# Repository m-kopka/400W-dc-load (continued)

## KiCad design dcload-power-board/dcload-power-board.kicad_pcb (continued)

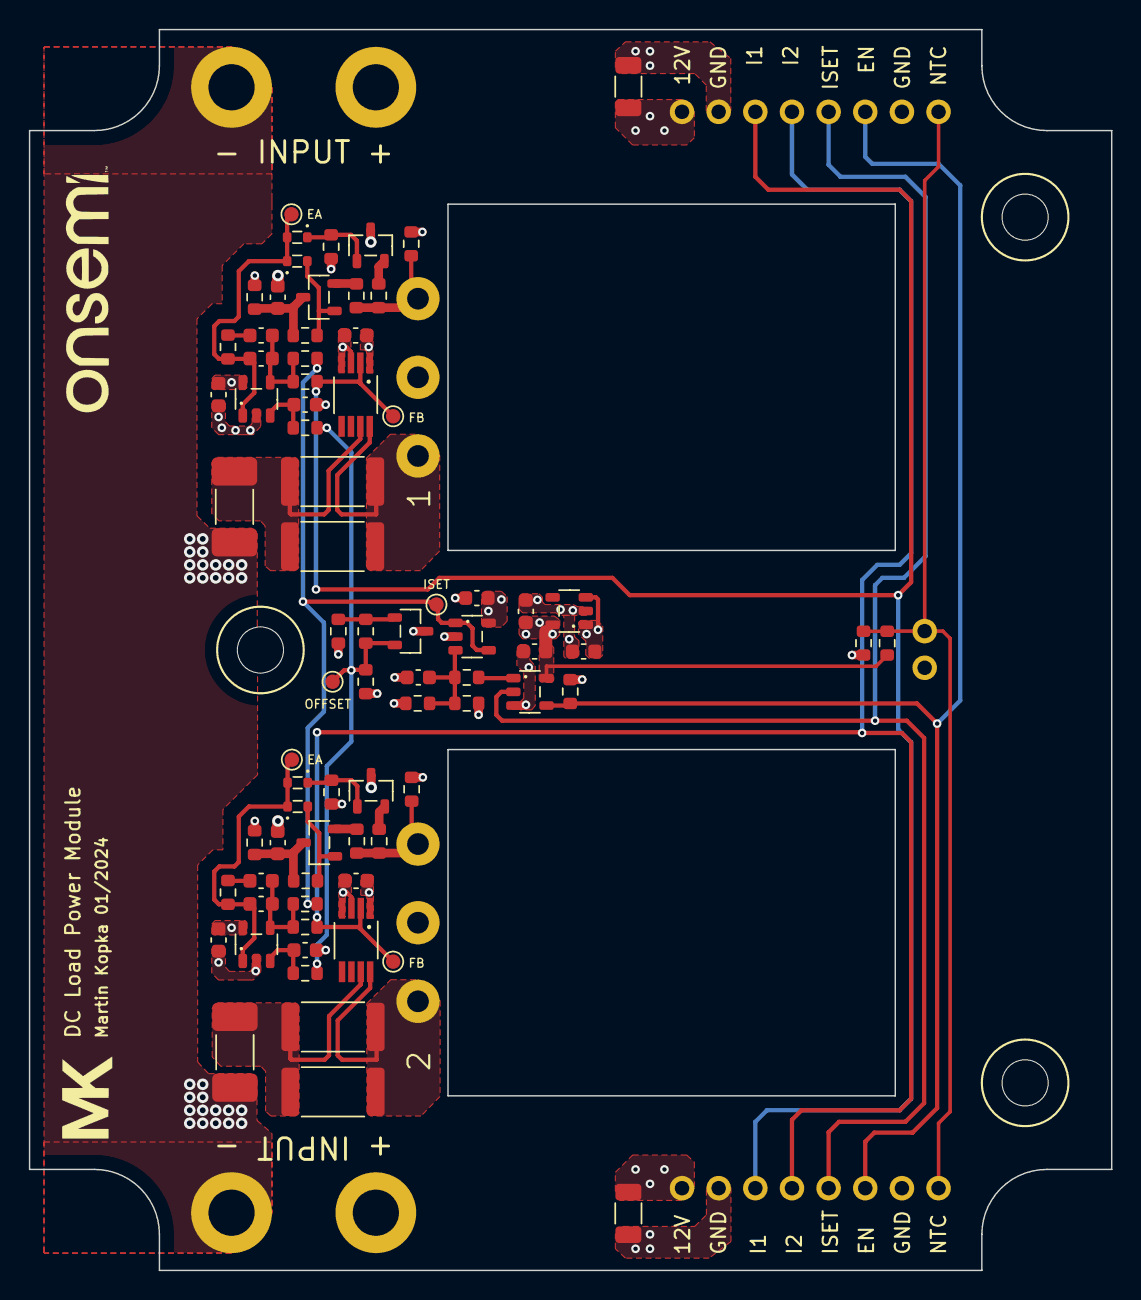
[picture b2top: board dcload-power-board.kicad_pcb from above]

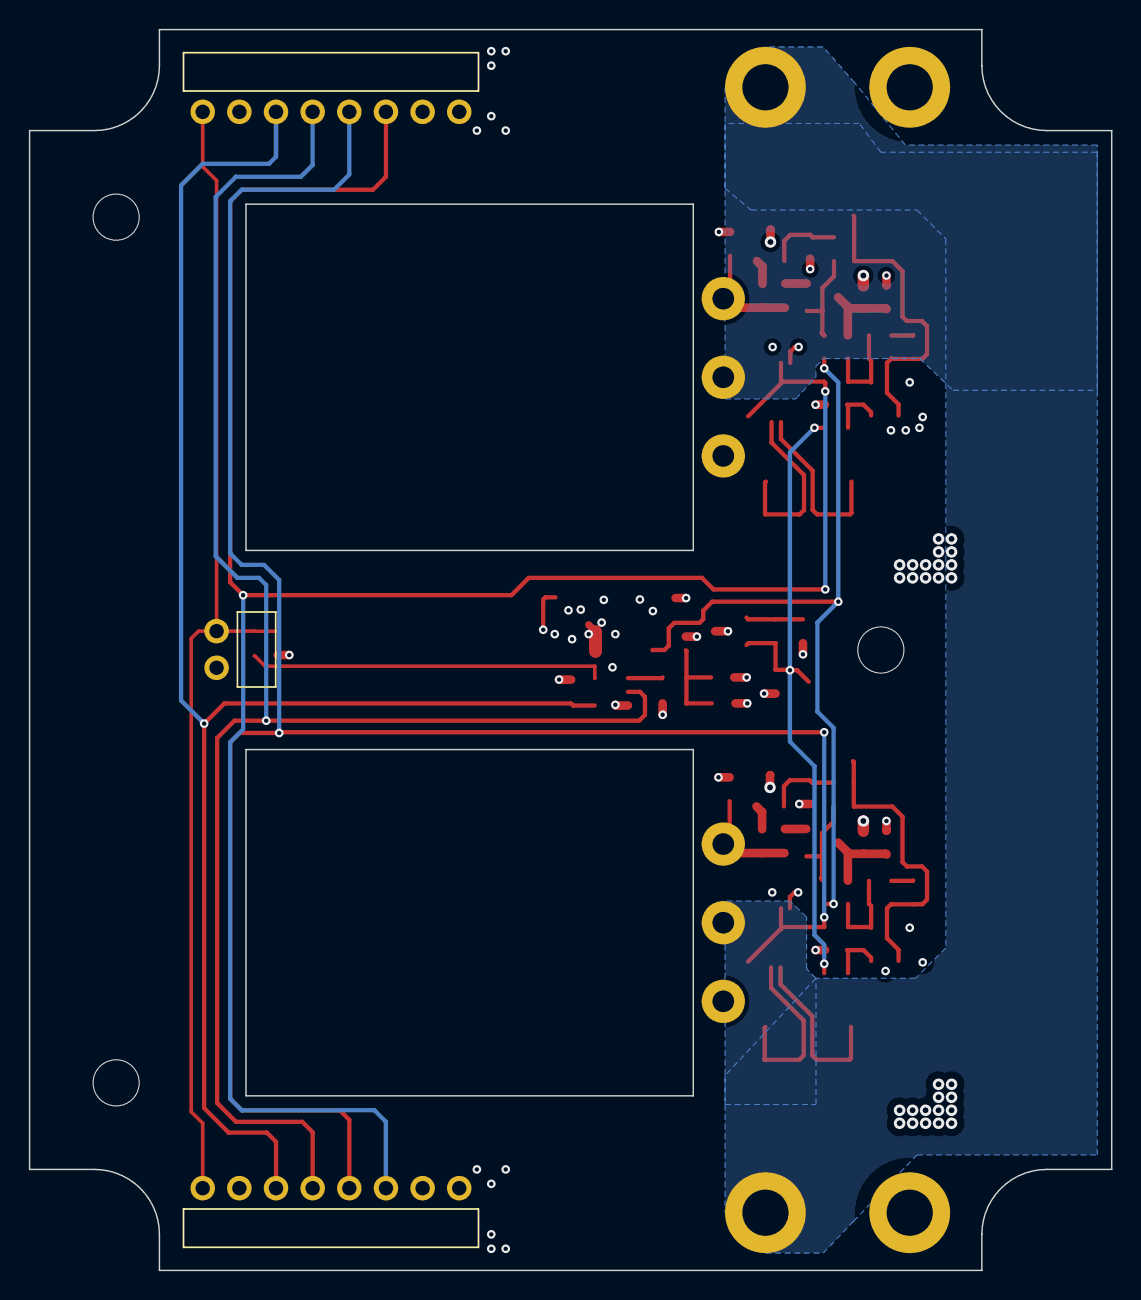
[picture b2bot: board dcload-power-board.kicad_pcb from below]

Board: 4 copper layers, 75.0 x 86.0 mm, 88 parts (3 on the bottom side), 38 nets.

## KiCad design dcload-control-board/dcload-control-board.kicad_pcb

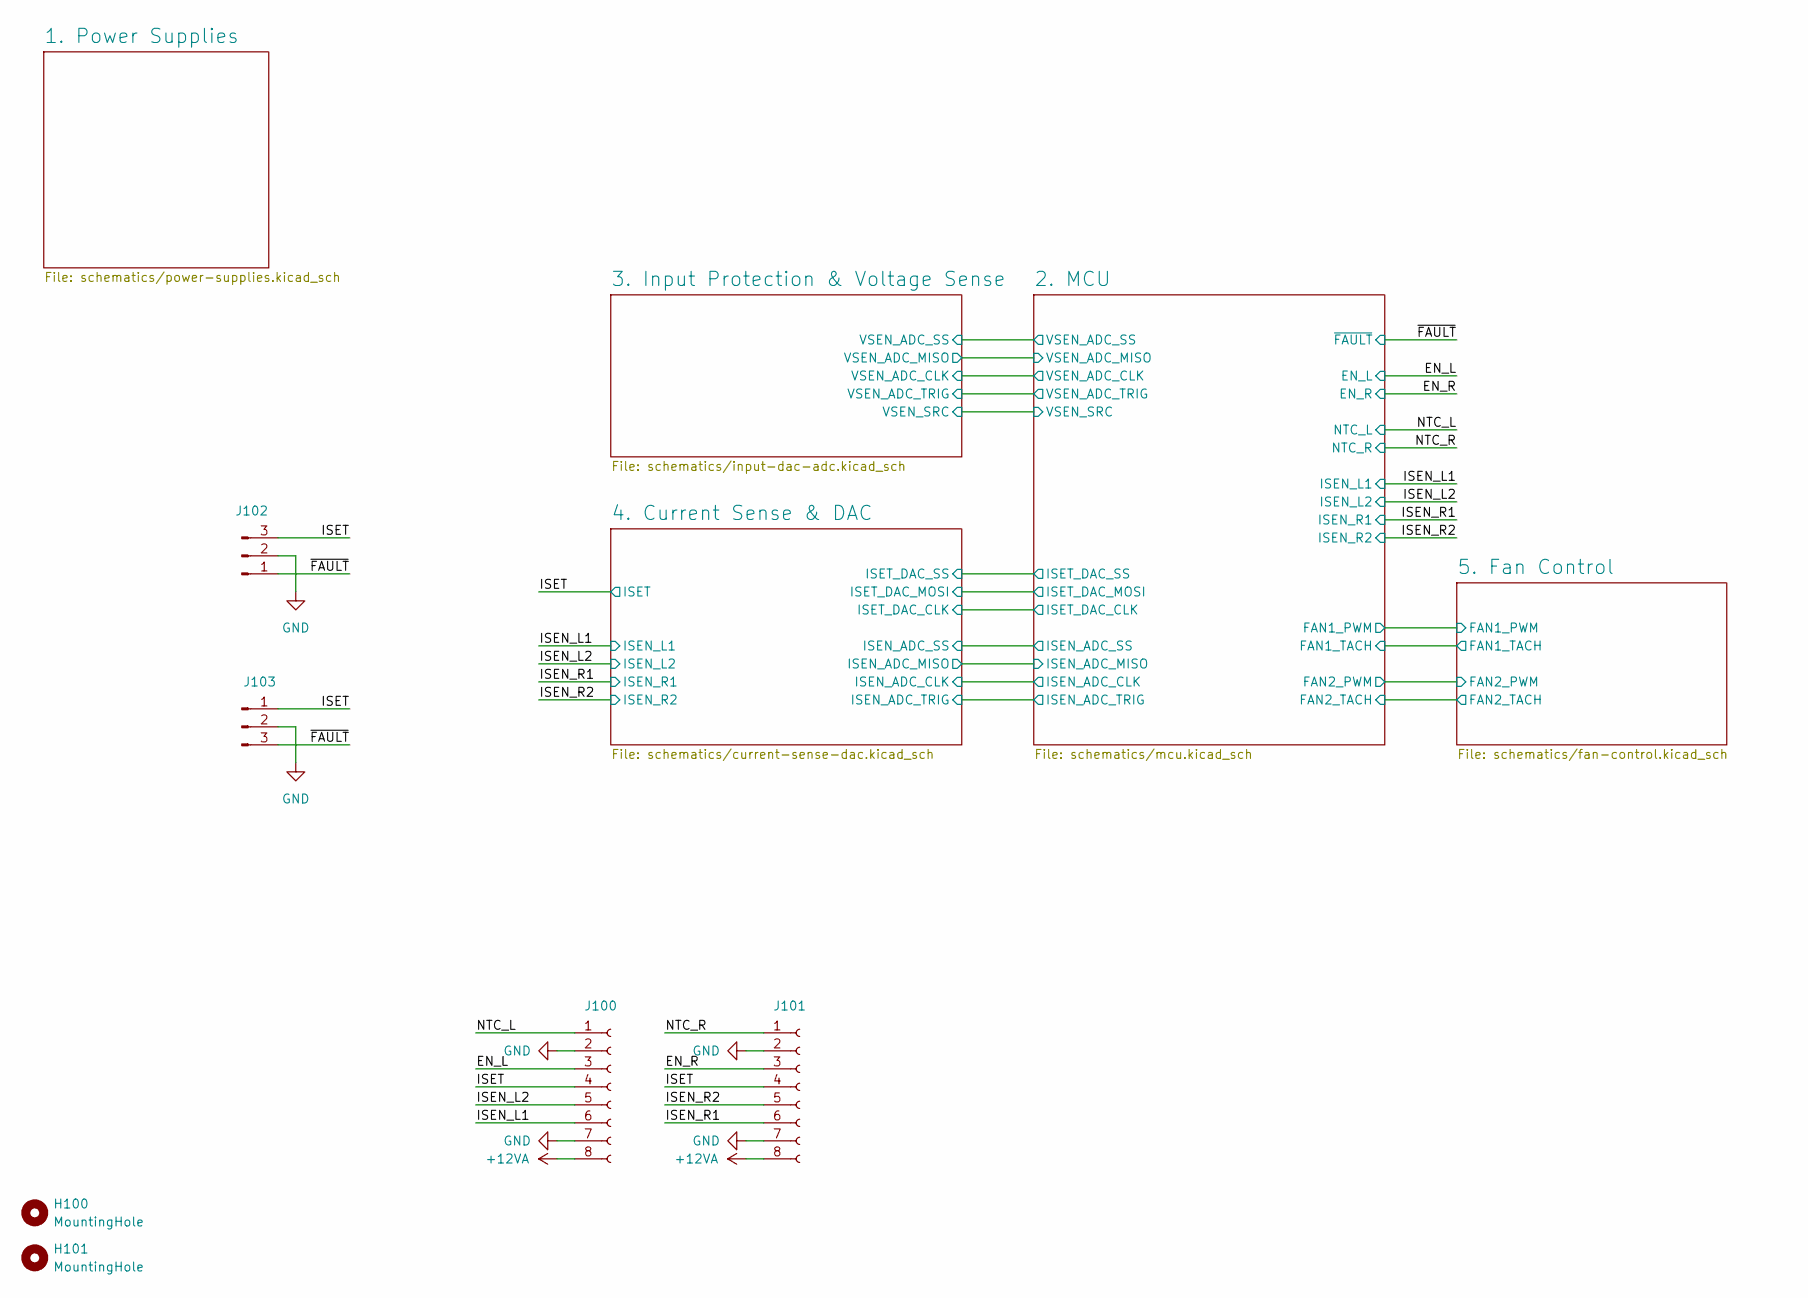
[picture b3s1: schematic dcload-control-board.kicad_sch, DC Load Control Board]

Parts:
H100, H101: MountingHole; MountingHole_3.2mm_M3
J100, J101: Conn_01x08_Female; PinSocket_1x08_P2.54mm_Vertical
J102, J103: Conn_01x03_Male; PinHeader_1x03_P2.54mm_Horizontal

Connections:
+12VA: J100.8, J101.8; also elsewhere on the board
/EN_L: J100.3; also elsewhere on the board
/EN_R: J101.3; also elsewhere on the board
/ISEN_L1: J100.6; also elsewhere on the board
/ISEN_L2: J100.5; also elsewhere on the board
/ISEN_R1: J101.6; also elsewhere on the board
/ISEN_R2: J101.5; also elsewhere on the board
/ISET: J100.4, J101.4, J102.3, J103.1; also elsewhere on the board
/NTC_L: J100.1; also elsewhere on the board
/NTC_R: J101.1; also elsewhere on the board
/~FAULT: J102.1, J103.3; also elsewhere on the board
GND: J100.2, J100.7, J101.2, J101.7, J102.2, J103.2; also elsewhere on the board

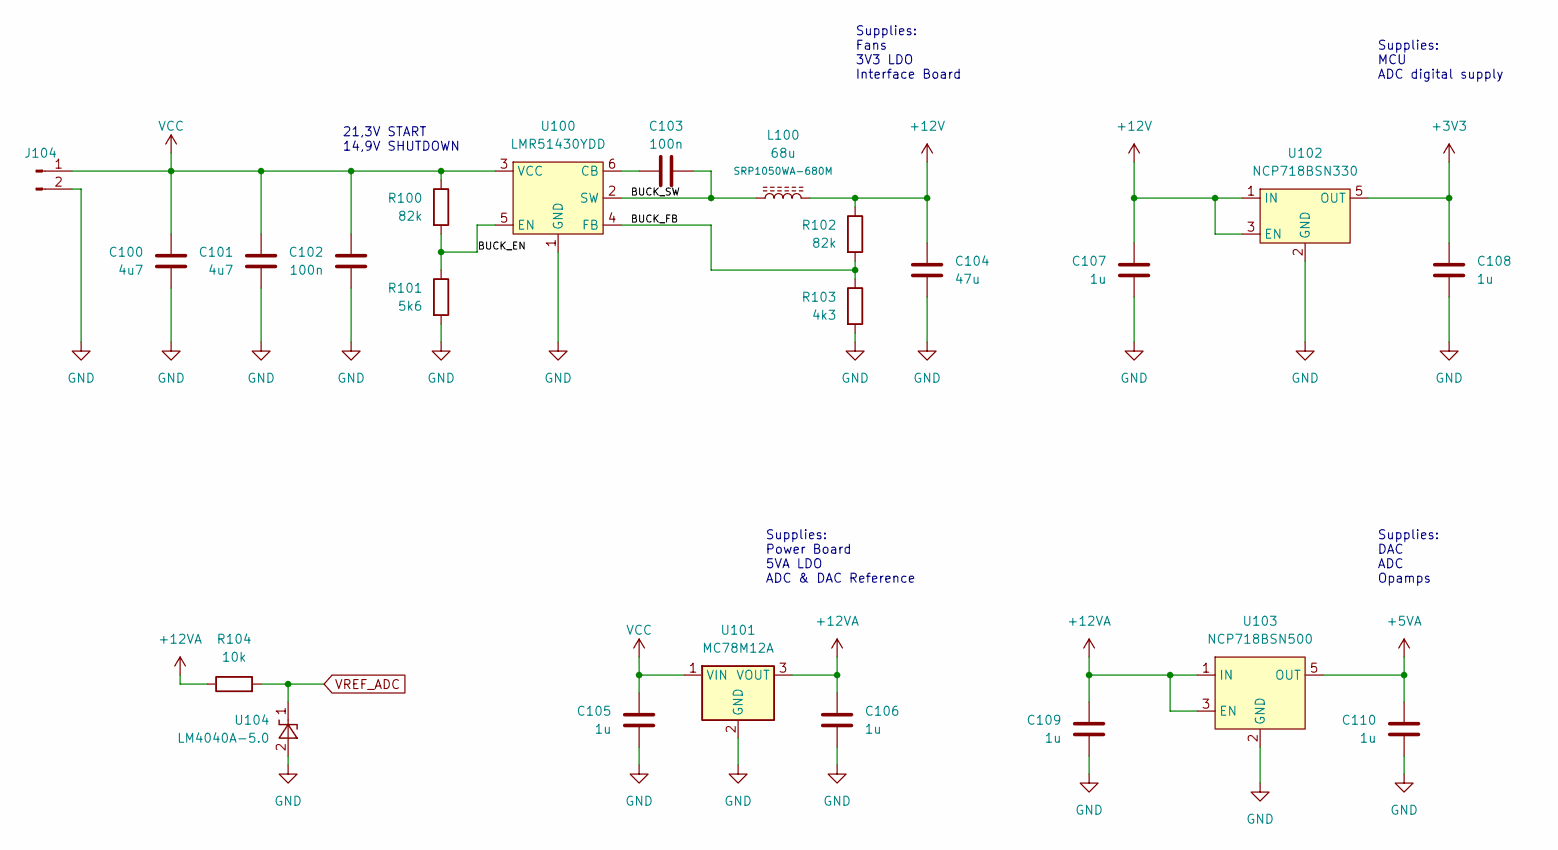
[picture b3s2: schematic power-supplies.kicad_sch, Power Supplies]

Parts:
C100, C101: 4u7; C_1206_3216Metric
C102, C103: 100n; C_0603_1608Metric
C104: 47u; C_1206_3216Metric
C105: 1u; C_1206_3216Metric
C106, C107, C108, C109, C110: 1u; C_0603_1608Metric
J104: Conn_01x02_Male; KLS PSH02-02W
L100: 68u; L_10.4x10.4_H4.8
R100, R102: 82k; R_0603_1608Metric
R101: 5k6; R_0603_1608Metric
R103: 4k3; R_0603_1608Metric
R104: 10k; R_0603_1608Metric
U100: LMR51430YDD; SOP-6
U101: MC78M12A; TO-252-2
U102: NCP718BSN330; SOT-23-5L
U103: NCP718BSN500; SOT-23-5L
U104: LM4040A-5.0; SOT-23

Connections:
+3V3: C108.2, U102.5 (OUT); also elsewhere on the board
+5VA: C110.2, U103.5 (OUT); also elsewhere on the board
+12V: C104.1, C107.2, L100.2, R102.1, U102.1 (IN), U102.3 (EN); also elsewhere on the board
+12VA: C106.2, C109.2, R104.1, U101.3 (VOUT), U103.1 (IN), U103.3 (EN); also elsewhere on the board
/1. Power Supplies/BUCK_EN: R100.2, R101.1, U100.5 (EN)
/1. Power Supplies/BUCK_FB: R102.2, R103.1, U100.4 (FB)
/1. Power Supplies/BUCK_SW: C103.2, L100.1, U100.2 (SW)
GND: C100.2, C101.2, C102.2, C104.2, C105.1, C106.1, C107.1, C108.1, C109.1, C110.1, J104.2, R101.2, R103.2, U100.1 (GND), U101.2 (GND), U102.2 (GND), U103.2 (GND), U104.2 (A); also elsewhere on the board
unnamed: C103.1, U100.6 (CB)
VCC: C100.1, C101.1, C102.1, C105.2, J104.1, R100.1, U100.3 (VCC), U101.1 (VIN)
VREF_ADC: R104.2, U104.1 (K); also elsewhere on the board

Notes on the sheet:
Supplies: Power Board 5VA LDO ADC & DAC Reference
Supplies: DAC ADC Opamps
21,3V START 14,9V SHUTDOWN
Supplies: MCU ADC digital supply
Supplies: Fans 3V3 LDO Interface Board

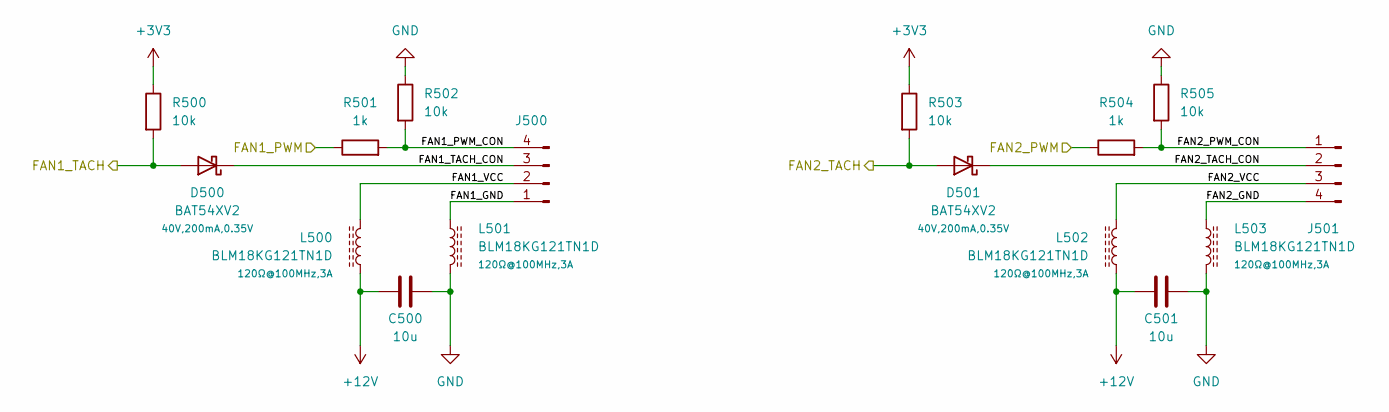
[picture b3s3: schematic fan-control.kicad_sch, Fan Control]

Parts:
C500, C501: 10u; C_1206_3216Metric
D500, D501: BAT54XV2; SOD-523
J500, J501: Conn_01x04_Male; PinHeader_1x04_P2.54mm_Horizontal
L500, L501, L502, L503: BLM18KG121TN1D; R_0603_1608Metric
R500, R502, R503, R505: 10k; R_0603_1608Metric
R501, R504: 1k; R_0603_1608Metric

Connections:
+3V3: R500.1, R503.1; also elsewhere on the board
+12V: C500.1, C501.1, L500.1, L502.1; also elsewhere on the board
/2. MCU/FAN1_PWM: R501.1; also elsewhere on the board
/2. MCU/FAN1_TACH: D500.2 (A), R500.2; also elsewhere on the board
/2. MCU/FAN2_PWM: R504.1; also elsewhere on the board
/2. MCU/FAN2_TACH: D501.2 (A), R503.2; also elsewhere on the board
/5. Fan Control/FAN1_GND: J500.1, L501.1
/5. Fan Control/FAN1_PWM_CON: J500.4, R501.2, R502.2
/5. Fan Control/FAN1_TACH_CON: D500.1 (K), J500.3
/5. Fan Control/FAN1_VCC: J500.2, L500.2
/5. Fan Control/FAN2_GND: J501.4, L503.1
/5. Fan Control/FAN2_PWM_CON: J501.1, R504.2, R505.2
/5. Fan Control/FAN2_TACH_CON: D501.1 (K), J501.2
/5. Fan Control/FAN2_VCC: J501.3, L502.2
GND: C500.2, C501.2, L501.2, L503.2, R502.1, R505.1; also elsewhere on the board

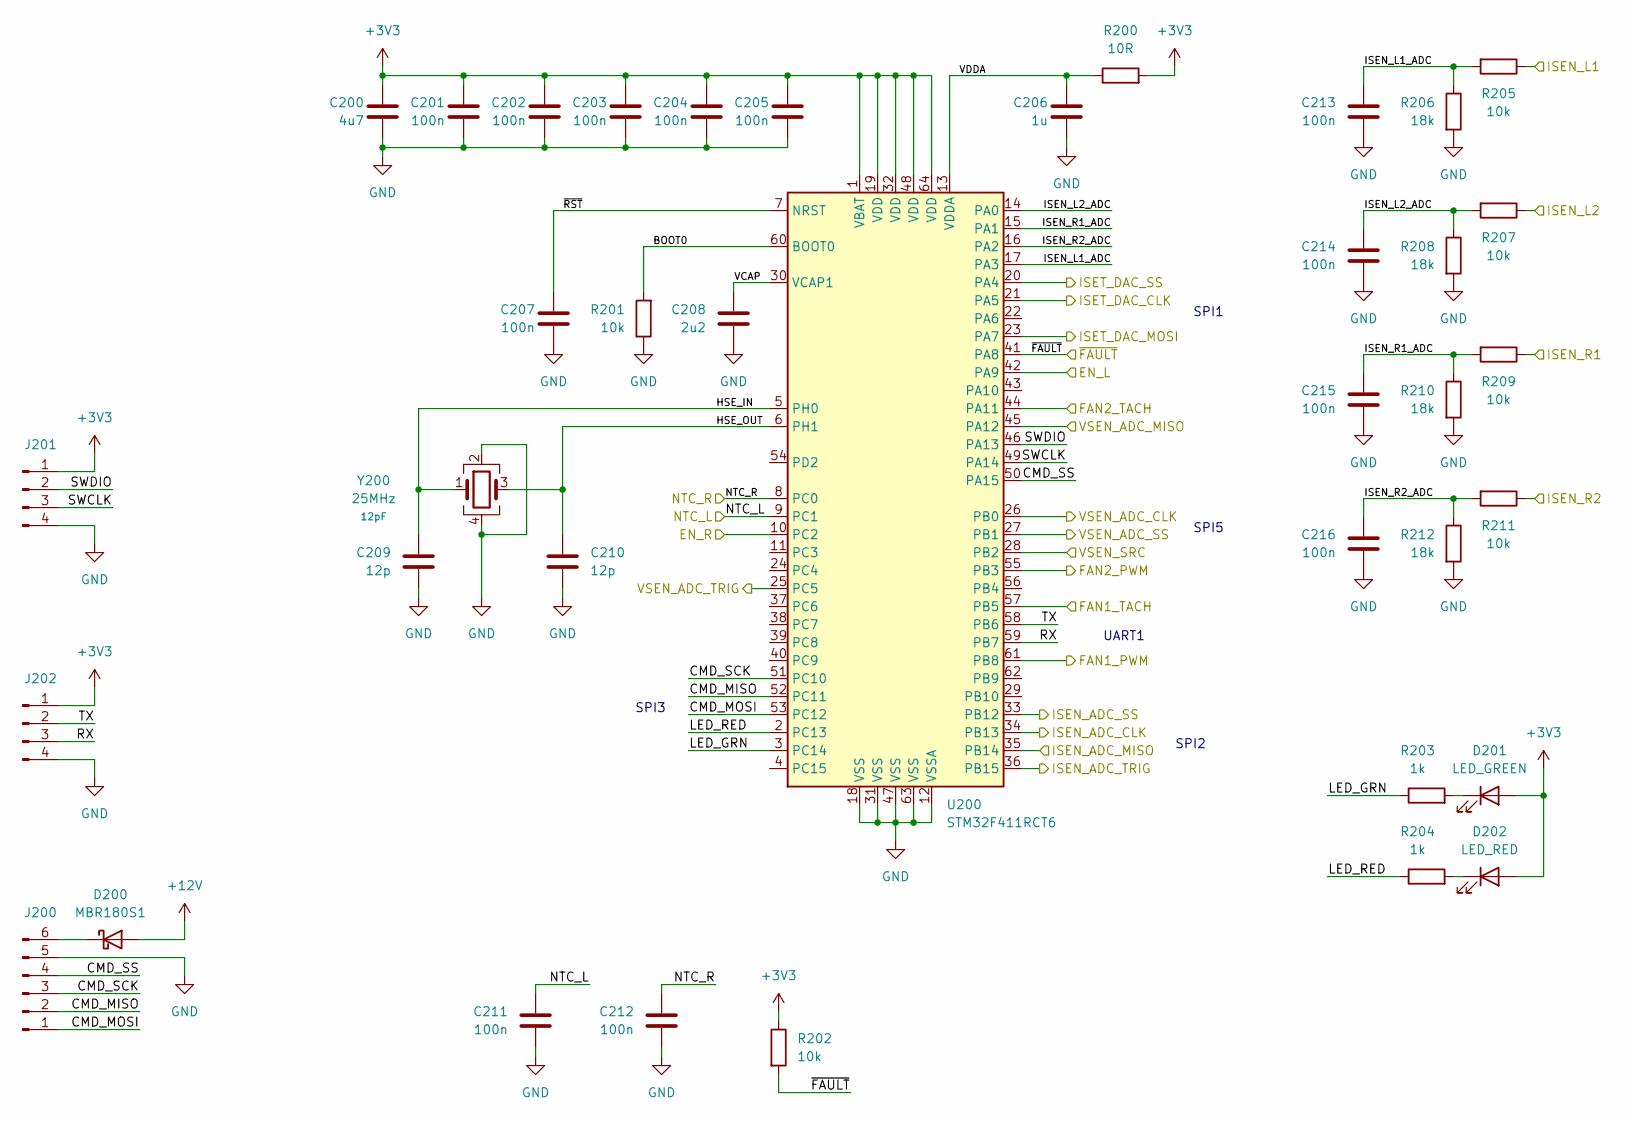
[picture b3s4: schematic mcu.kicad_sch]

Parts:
C200: 4u7; C_0603_1608Metric
C201, C202, C203, C204, C205, C207, C211, C212, C213, C214, C215, C216: 100n; C_0603_1608Metric
C206: 1u; C_0603_1608Metric
C208: 2u2; C_0603_1608Metric
C209, C210: 12p; C_0603_1608Metric
D200: MBR180S1; SOD-123LF
D201: LED_GREEN; LED 0603
D202: LED_RED; LED 0603
J200: Conn_01x06_Male; PinHeader_1x06_P2.54mm_Horizontal
J201, J202: Conn_01x04_Male; PinHeader_1x04_P2.54mm_Vertical
R200: 10R; R_0603_1608Metric
R201, R202, R205, R207, R209, R211: 10k; R_0603_1608Metric
R203, R204: 1k; R_0603_1608Metric
R206, R208, R210, R212: 18k; R_0603_1608Metric
U200: STM32F411RCT6; LQFP-64_10x10mm_P0.5mm
Y200: 25MHz; Crystal 3225 3.2x2.5mm 4pin; Part ECS-250-12-33-AGN-TR3

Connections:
+3V3: C200.1, C201.1, C202.1, C203.1, C204.1, C205.1, D201.2 (A), D202.2 (A), J201.1, J202.1, R200.2, R202.1, U200.1 (VBAT), U200.19 (VDD), U200.32 (VDD), U200.48 (VDD), U200.64 (VDD); also elsewhere on the board
+12V: D200.2 (A); also elsewhere on the board
/2. MCU/BOOT0: R201.2, U200.60 (BOOT0)
/2. MCU/CMD_MISO: J200.2, U200.52 (PC11)
/2. MCU/CMD_MOSI: J200.1, U200.53 (PC12)
/2. MCU/CMD_SCK: J200.3, U200.51 (PC10)
/2. MCU/CMD_SS: J200.4, U200.50 (PA15)
/2. MCU/FAN1_PWM: U200.61 (PB8); also elsewhere on the board
/2. MCU/FAN1_TACH: U200.57 (PB5); also elsewhere on the board
/2. MCU/FAN2_PWM: U200.55 (PB3); also elsewhere on the board
/2. MCU/FAN2_TACH: U200.44 (PA11); also elsewhere on the board
/2. MCU/HSE_IN: C209.1, U200.5 (PH0), Y200.1
/2. MCU/HSE_OUT: C210.1, U200.6 (PH1), Y200.3
/2. MCU/ISEN_ADC_CLK: U200.34 (PB13); also elsewhere on the board
/2. MCU/ISEN_ADC_MISO: U200.35 (PB14); also elsewhere on the board
/2. MCU/ISEN_ADC_SS: U200.33 (PB12); also elsewhere on the board
/2. MCU/ISEN_ADC_TRIG: U200.36 (PB15); also elsewhere on the board
/2. MCU/ISEN_L1_ADC: C213.1, R205.2, R206.1, U200.17 (PA3)
/2. MCU/ISEN_L2_ADC: C214.1, R207.2, R208.1, U200.14 (PA0)
/2. MCU/ISEN_R1_ADC: C215.1, R209.2, R210.1, U200.15 (PA1)
/2. MCU/ISEN_R2_ADC: C216.1, R211.2, R212.1, U200.16 (PA2)
/2. MCU/ISET_DAC_CLK: U200.21 (PA5); also elsewhere on the board
/2. MCU/ISET_DAC_MOSI: U200.23 (PA7); also elsewhere on the board
/2. MCU/ISET_DAC_SS: U200.20 (PA4); also elsewhere on the board
/2. MCU/LED_GRN: R203.1, U200.3 (PC14)
/2. MCU/LED_RED: R204.1, U200.2 (PC13)
/2. MCU/RX: J202.3, U200.59 (PB7)
/2. MCU/SWCLK: J201.3, U200.49 (PA14)
/2. MCU/SWDIO: J201.2, U200.46 (PA13)
/2. MCU/TX: J202.2, U200.58 (PB6)
/2. MCU/VCAP: C208.1, U200.30 (VCAP1)
/2. MCU/VDDA: C206.1, R200.1, U200.13 (VDDA)
/2. MCU/VSEN_ADC_CLK: U200.26 (PB0); also elsewhere on the board
/2. MCU/VSEN_ADC_MISO: U200.45 (PA12); also elsewhere on the board
/2. MCU/VSEN_ADC_SS: U200.27 (PB1); also elsewhere on the board
/2. MCU/VSEN_ADC_TRIG: U200.25 (PC5); also elsewhere on the board
/2. MCU/VSEN_SRC: U200.28 (PB2); also elsewhere on the board
/2. MCU/~RST: C207.1, U200.7 (NRST)
/EN_L: U200.42 (PA9); also elsewhere on the board
/EN_R: U200.10 (PC2); also elsewhere on the board
/ISEN_L1: R205.1; also elsewhere on the board
/ISEN_L2: R207.1; also elsewhere on the board
/ISEN_R1: R209.1; also elsewhere on the board
/ISEN_R2: R211.1; also elsewhere on the board
/NTC_L: C211.1, U200.9 (PC1); also elsewhere on the board
/NTC_R: C212.1, U200.8 (PC0); also elsewhere on the board
/~FAULT: R202.2, U200.41 (PA8); also elsewhere on the board
GND: C200.2, C201.2, C202.2, C203.2, C204.2, C205.2, C206.2, C207.2, C208.2, C209.2, C210.2, C211.2, C212.2, C213.2, C214.2, C215.2, C216.2, J200.5, J201.4, J202.4, R201.1, R206.2, R208.2, R210.2, R212.2, U200.12 (VSSA), U200.18 (VSS), U200.31 (VSS), U200.47 (VSS), U200.63 (VSS), Y200.2, Y200.4; also elsewhere on the board
unnamed: D200.1 (K), J200.6
unnamed: D201.1 (K), R203.2
unnamed: D202.1 (K), R204.2

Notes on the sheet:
SPI3
SPI1
SPI2
SPI5
UART1

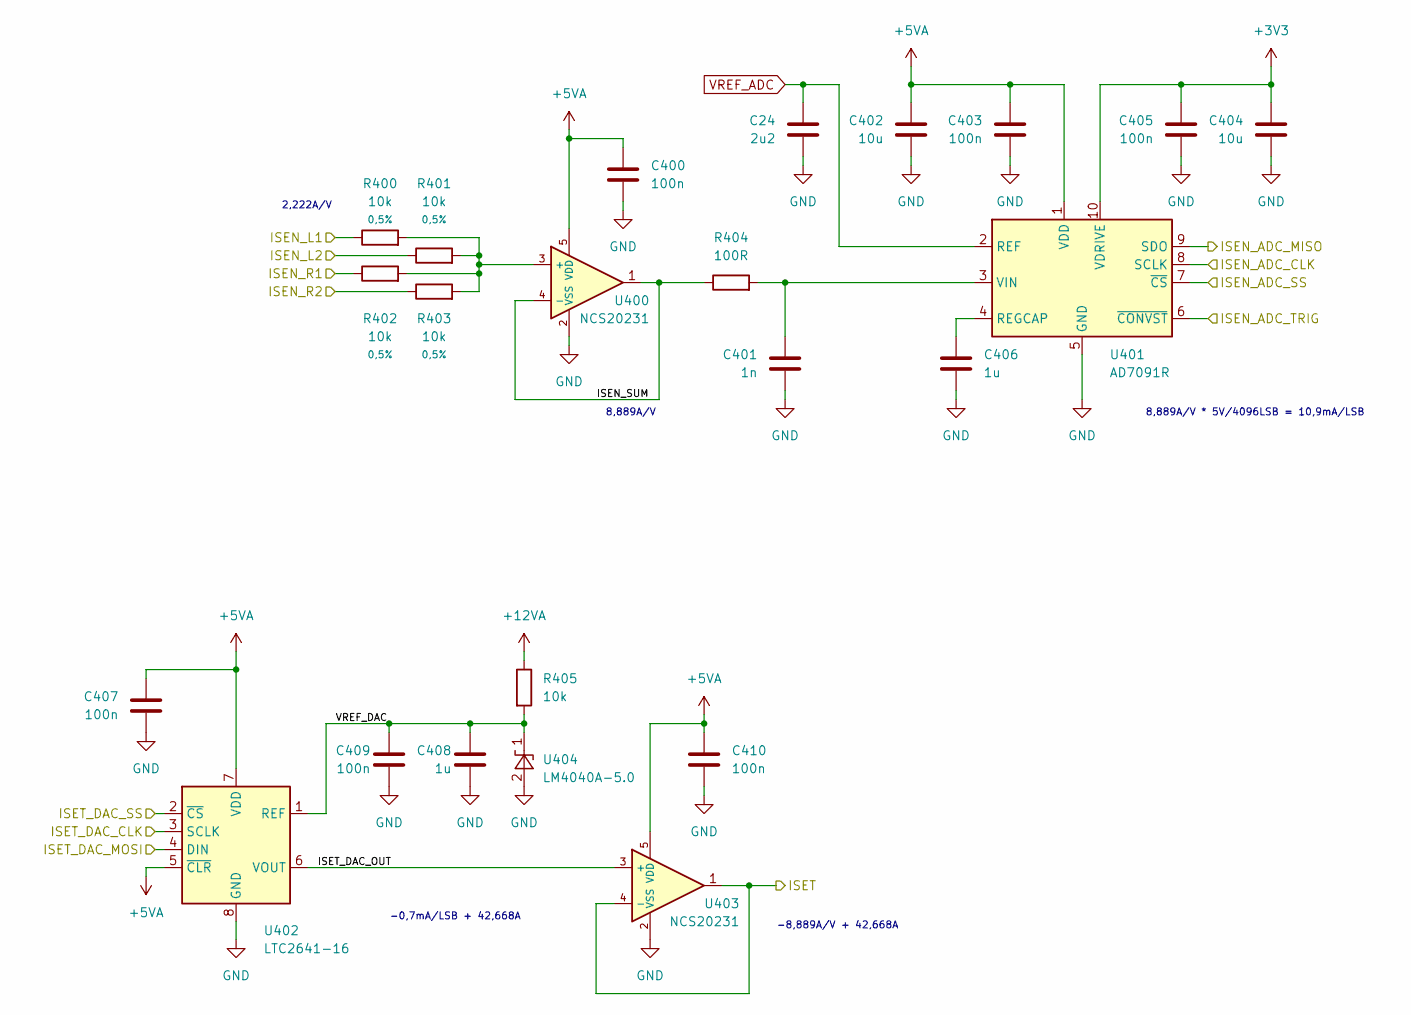
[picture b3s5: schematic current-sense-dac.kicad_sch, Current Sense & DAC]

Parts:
C24: 2u2; C_0603_1608Metric
C400, C403, C405, C407, C409, C410: 100n; C_0603_1608Metric
C401: 1n; C_0603_1608Metric
C402, C404: 10u; C_0603_1608Metric
C406, C408: 1u; C_0603_1608Metric
R400, R401, R402, R403: 10k; R_0603_1608Metric; Tolerance 0,5%
R404: 100R; R_0603_1608Metric
R405: 10k; R_0603_1608Metric
U400, U403: NCS20231; SOT-23-5L
U401: AD7091R; VSSOP-10 3x3mm P0.5mm
U402: LTC2641-16; VSSOP-8_3x3mm_P0.65mm
U404: LM4040A-5.0; SOT-23

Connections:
+3V3: C404.1, C405.1, U401.10 (VDRIVE); also elsewhere on the board
+5VA: C400.1, C402.1, C403.1, C407.1, C410.1, U400.5 (VDD), U401.1 (VDD), U402.5 (~CLR), U402.7 (VDD), U403.5 (VDD); also elsewhere on the board
+12VA: R405.1; also elsewhere on the board
/2. MCU/ISEN_ADC_CLK: U401.8 (SCLK); also elsewhere on the board
/2. MCU/ISEN_ADC_MISO: U401.9 (SDO); also elsewhere on the board
/2. MCU/ISEN_ADC_SS: U401.7 (~CS); also elsewhere on the board
/2. MCU/ISEN_ADC_TRIG: U401.6 (~CONVST); also elsewhere on the board
/2. MCU/ISET_DAC_CLK: U402.3 (SCLK); also elsewhere on the board
/2. MCU/ISET_DAC_MOSI: U402.4 (DIN); also elsewhere on the board
/2. MCU/ISET_DAC_SS: U402.2 (~CS); also elsewhere on the board
/4. Current Sense & DAC/ISEN_SUM: R404.1, U400.1, U400.4 (-)
/4. Current Sense & DAC/ISET_DAC_OUT: U402.6 (VOUT), U403.3 (+)
/4. Current Sense & DAC/VREF_DAC: C408.1, C409.1, R405.2, U402.1 (REF), U404.1 (K)
/ISEN_L1: R400.1; also elsewhere on the board
/ISEN_L2: R401.1; also elsewhere on the board
/ISEN_R1: R402.1; also elsewhere on the board
/ISEN_R2: R403.1; also elsewhere on the board
/ISET: U403.1, U403.4 (-); also elsewhere on the board
GND: C24.1, C400.2, C401.2, C402.2, C403.2, C404.2, C405.2, C406.2, C407.2, C408.2, C409.2, C410.2, U400.2 (VSS), U401.5 (GND), U402.8 (GND), U403.2 (VSS), U404.2 (A); also elsewhere on the board
unnamed: C401.1, R404.2, U401.3 (VIN)
unnamed: C406.1, U401.4 (REGCAP)
unnamed: R400.2, R401.2, R402.2, R403.2, U400.3 (+)
VREF_ADC: C24.2, U401.2 (REF); also elsewhere on the board

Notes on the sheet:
8,889A/V * 5V/4096LSB = 10,9mA/LSB
-0,7mA/LSB + 42,668A
-8,889A/V + 42,668A
2,222A/V
8,889A/V

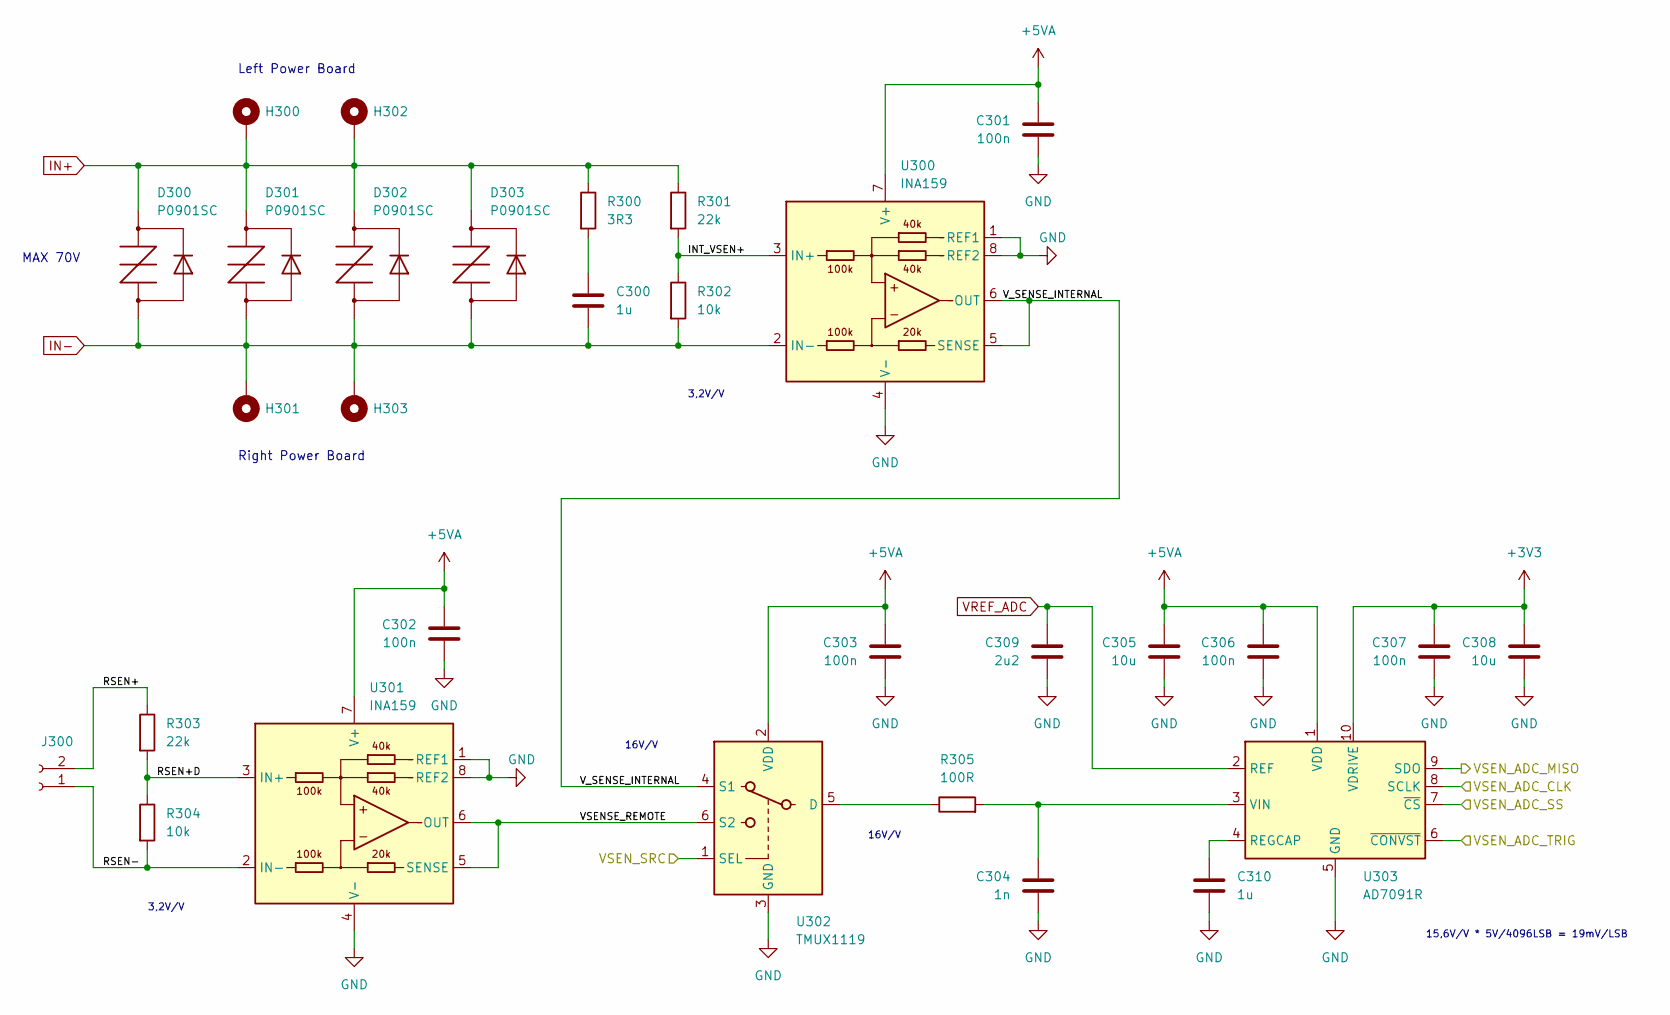
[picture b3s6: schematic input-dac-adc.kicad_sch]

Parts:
C300: 1u; C_1206_3216Metric
C301, C302, C303, C306, C307: 100n; C_0603_1608Metric
C304: 1n; C_0603_1608Metric
C305, C308: 10u; C_0603_1608Metric
C309: 2u2; C_0603_1608Metric
C310: 1u; C_0603_1608Metric
D300, D301, D302, D303: P0901SC; SMB
H300, H301, H302, H303: MountingHole_Pad; MountingHole_4.3mm_M4_DIN965_Pad
J300: Conn_01x02_Female; JST_XH_B2B-XH-A_1x02_P2.50mm_Vertical
R300: 3R3; R_1206_3216Metric
R301, R303: 22k; R_0603_1608Metric
R302, R304: 10k; R_0603_1608Metric
R305: 100R; R_0603_1608Metric
U300, U301: INA159; VSSOP-8_3x3mm_P0.65mm
U302: TMUX1119; SOP-6
U303: AD7091R; VSSOP-10 3x3mm P0.5mm

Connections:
+3V3: C307.1, C308.1, U303.10 (VDRIVE); also elsewhere on the board
+5VA: C301.1, C302.1, C303.1, C305.1, C306.1, U300.7 (V+), U301.7 (V+), U302.2 (VDD), U303.1 (VDD); also elsewhere on the board
/2. MCU/VSEN_ADC_CLK: U303.8 (SCLK); also elsewhere on the board
/2. MCU/VSEN_ADC_MISO: U303.9 (SDO); also elsewhere on the board
/2. MCU/VSEN_ADC_SS: U303.7 (~CS); also elsewhere on the board
/2. MCU/VSEN_ADC_TRIG: U303.6 (~CONVST); also elsewhere on the board
/2. MCU/VSEN_SRC: U302.1 (SEL); also elsewhere on the board
/3. Input Protection & Voltage Sense/INT_VSEN+: R301.2, R302.1, U300.3 (IN+)
/3. Input Protection & Voltage Sense/RSEN+: J300.2, R303.1
/3. Input Protection & Voltage Sense/RSEN+D: R303.2, R304.1, U301.3 (IN+)
/3. Input Protection & Voltage Sense/RSEN-: J300.1, R304.2, U301.2 (IN-)
/3. Input Protection & Voltage Sense/VSENSE_REMOTE: U301.5 (SENSE), U301.6 (OUT), U302.6 (S2)
/3. Input Protection & Voltage Sense/V_SENSE_INTERNAL: U300.5 (SENSE), U300.6 (OUT), U302.4 (S1)
GND: C301.2, C302.2, C303.2, C304.2, C305.2, C306.2, C307.2, C308.2, C309.1, C310.2, U300.1 (REF1), U300.4 (V-), U300.8 (REF2), U301.1 (REF1), U301.4 (V-), U301.8 (REF2), U302.3 (GND), U303.5 (GND); also elsewhere on the board
IN+: D300.1 (G), D301.1 (G), D302.1 (G), D303.1 (G), H300.1, H302.1, R300.1, R301.1
IN-: C300.2, D300.2 (T/R), D301.2 (T/R), D302.2 (T/R), D303.2 (T/R), H301.1, H303.1, R302.2, U300.2 (IN-)
unnamed: C300.1, R300.2
unnamed: C304.1, R305.2, U303.3 (VIN)
unnamed: C310.1, U303.4 (REGCAP)
unnamed: R305.1, U302.5 (D)
VREF_ADC: C309.2, U303.2 (REF); also elsewhere on the board

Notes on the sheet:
Left Power Board
Right Power Board
3,2V/V
MAX 70V
16V/V
15,6V/V * 5V/4096LSB = 19mV/LSB

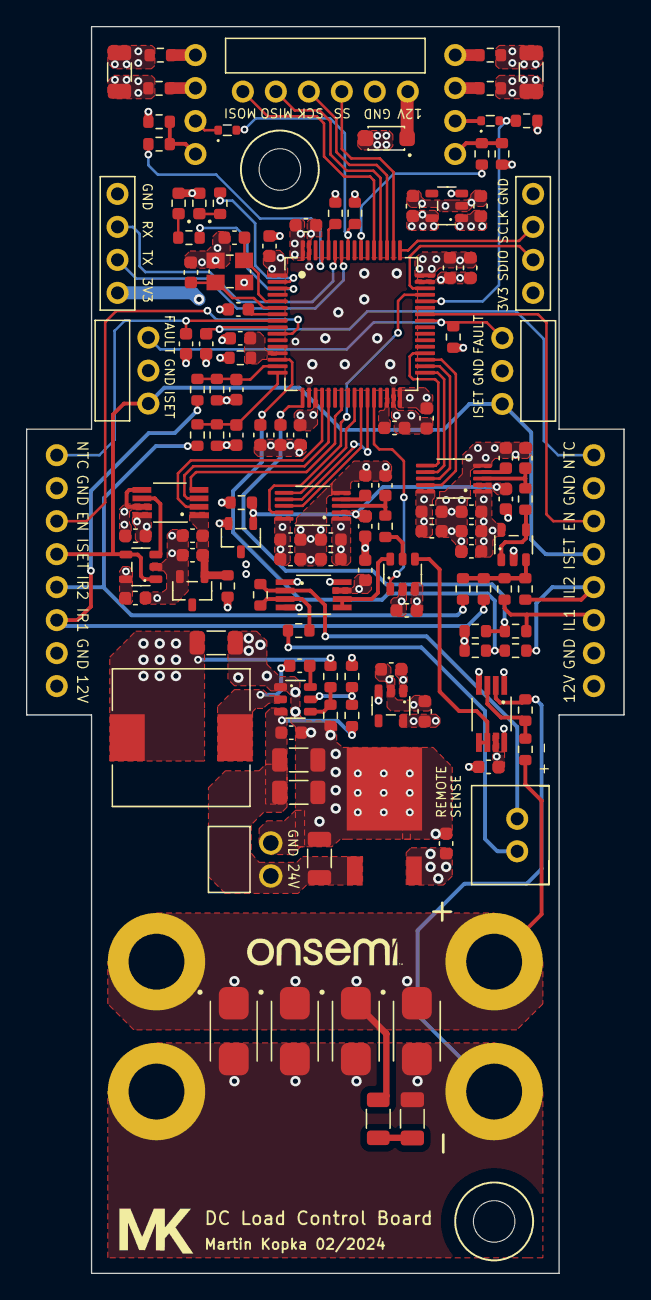
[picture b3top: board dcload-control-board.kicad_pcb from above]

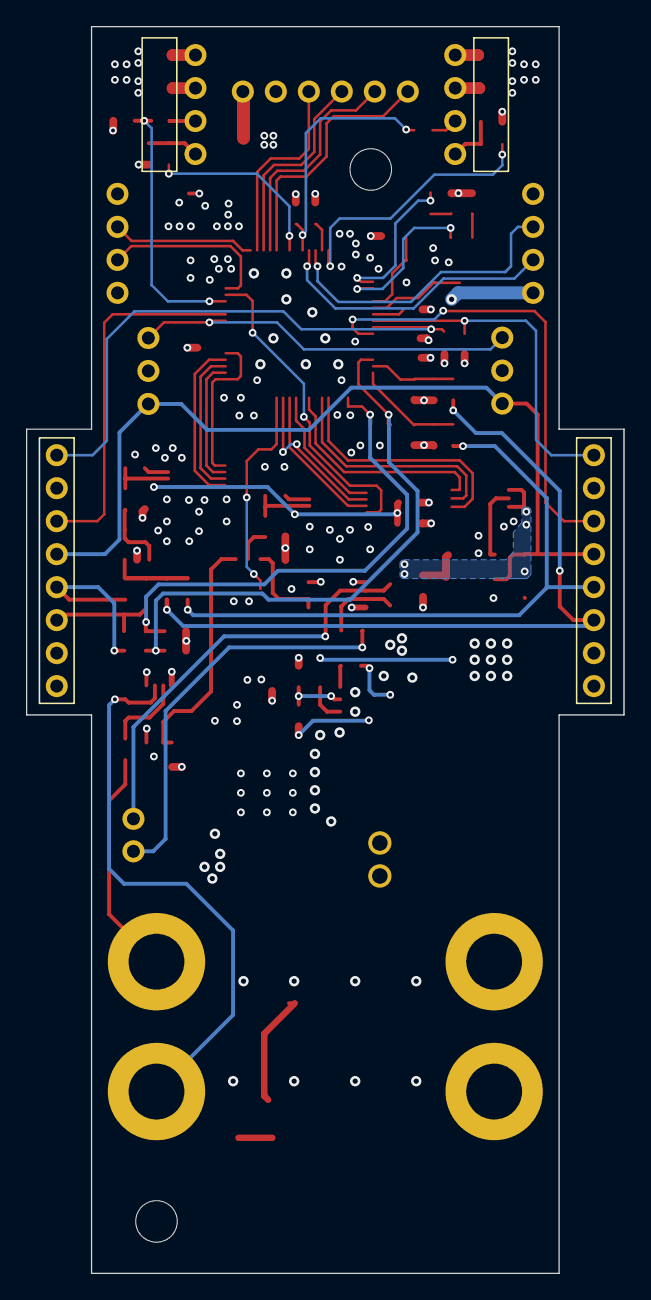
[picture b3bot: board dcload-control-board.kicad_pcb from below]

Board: 4 copper layers, 46.0 x 96.0 mm, 136 parts (4 on the bottom side), 86 nets.

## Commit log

2024-05-06 add: interface panel board
